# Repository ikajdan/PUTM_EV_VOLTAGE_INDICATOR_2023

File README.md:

# Voltage Indicator

This repository contains the hardware design files for a voltage indicator used in the accumulator of a Formula Student electric vehicle. The voltage indicator is a safety feature that provides a visual indication when the voltage exceeds a safe threshold. The voltage indicator is designed to meet the requirements of the Formula Student EV rulebook and ensure the safety of the accumulator during operation.

The rules state that the connection status must be clearly visible, and electrically controlled switches are not allowed. A visible indicator, such as a voltmeter or red LED, must illuminate when voltage exceeds 60 V DC or half the maximum TS voltage. This indicator must be clearly marked as a "Voltage Indicator", visible during disconnection, and function independently of software control, always powered by the TS, even when the accumulator is removed.

<br>
<div align="center">
  </img>
  <br><br>
  <em>PCB layout of the voltage indicator.</em>
</div>
<br>

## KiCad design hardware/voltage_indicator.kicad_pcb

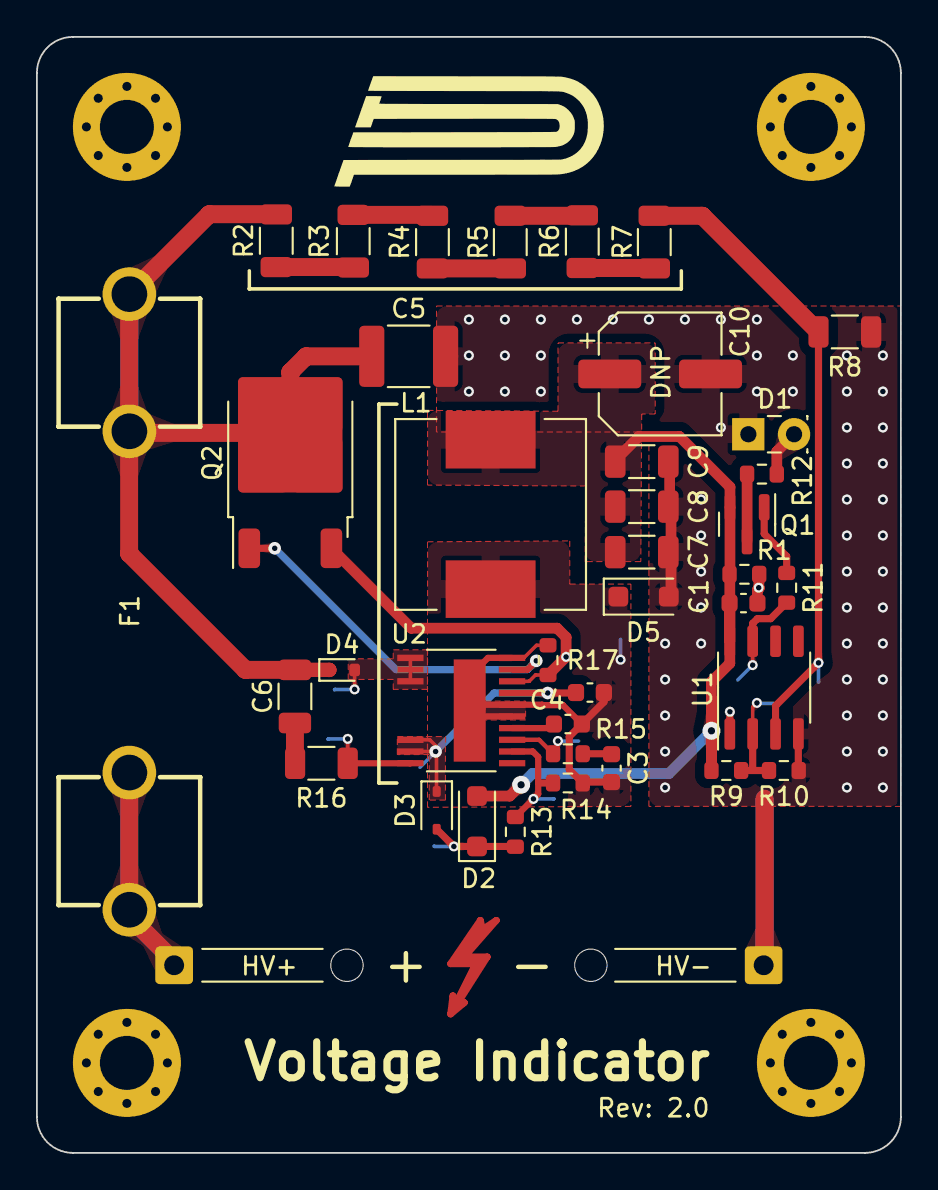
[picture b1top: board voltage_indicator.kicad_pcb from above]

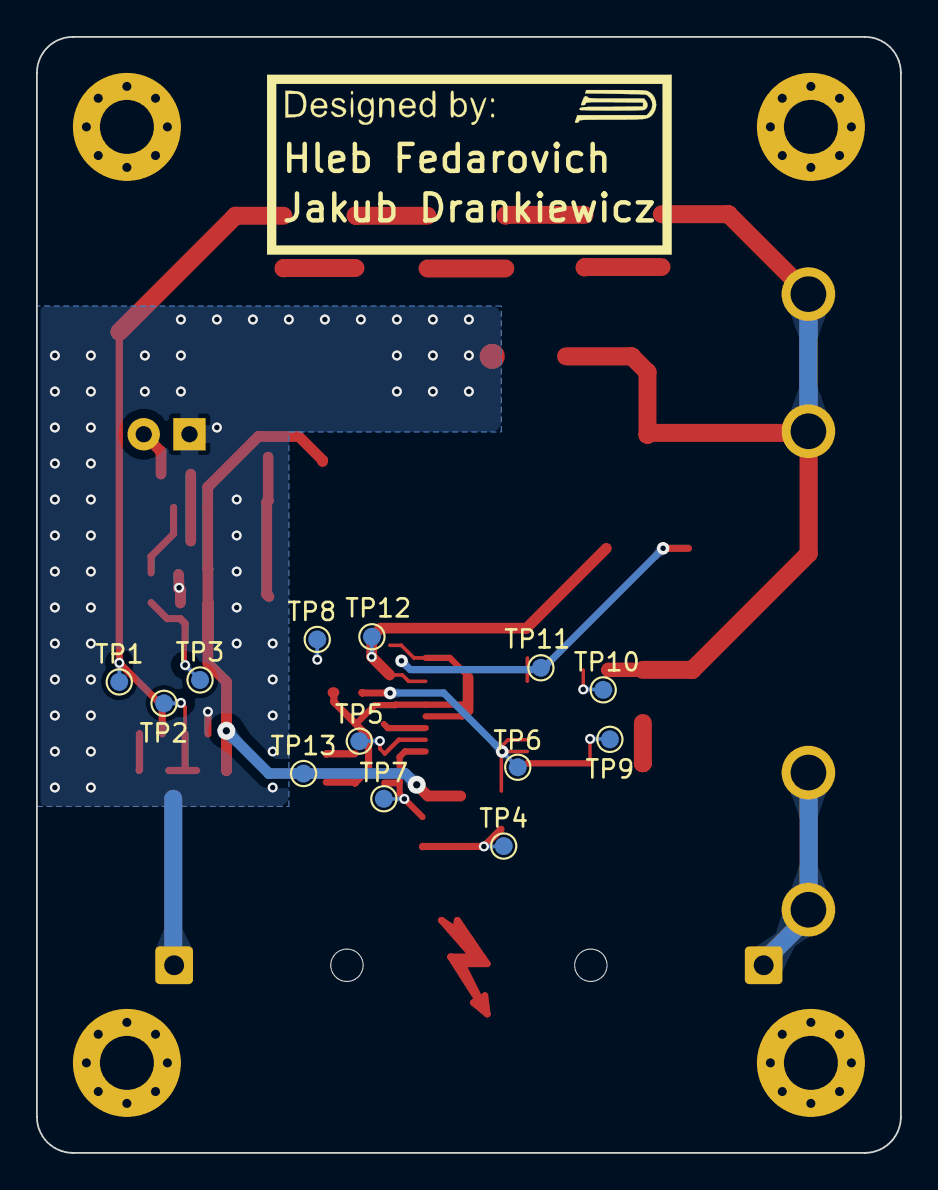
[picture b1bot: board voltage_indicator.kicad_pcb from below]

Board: 2 copper layers, 48.0 x 62.0 mm, 53 parts (13 on the bottom side), 27 nets.

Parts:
C1, C3, C4: 100n; C_0603_1608Metric
C2: 10u; C_0603_1608Metric
C5: 100n; C_1812_4532Metric
C6: 10p; C_1206_3216Metric
C7, C8, C9: 47u; C_1206_3216Metric
C10: 330u; CP_Elec_6.3x5.4
D1: Red; LED_Rectangular_W3.9mm_H1.9mm
D2, D5: US1KFA; D_SOD-123F
D3: CMDSH2-3; D_SOD-323
D4: 10V; D_SOD-523
F1: 600V; FuseClip
J1: HV+; SolderWire_Relief
J2: HV-; SolderWire_Relief
L1: 1m; WurthElektronikInductor_7687714102
Q1: BC807; SOT-23
Q2: TK3P80ERQ; TO-252-2
R1: 1k; R_0603_1608Metric
R2, R3, R4, R5, R6, R7: 100k; R_1206_3216Metric
R8, R16: 10k; R_1206_3216Metric
R9: 3k; R_0603_1608Metric
R10: 240R; R_0603_1608Metric
R11: 1k5; R_0603_1608Metric
R12: 470R; R_0603_1608Metric
R13: 21k5; R_0603_1608Metric
R14: 2k49; R_0603_1608Metric
R15: 22k1; R_0603_1608Metric
R17: 220m; R_0603_1608Metric
TP1: LM_N; TestPoint_Pad_D1.0mm
TP2: LM_P; TestPoint_Pad_D1.0mm
TP3: LM_OUT; TestPoint_Pad_D1.0mm
TP4: LT_D3; TestPoint_Pad_D1.0mm
TP5: LT_VC; TestPoint_Pad_D1.0mm
TP6: LT_BIAS; TestPoint_Pad_D1.0mm
TP7: LT_FB; TestPoint_Pad_D1.0mm
TP8: LT_GND; TestPoint_Pad_D1.0mm
TP9: LT_DCM; TestPoint_Pad_D1.0mm
TP10: LT_VIN; TestPoint_Pad_D1.0mm
TP11: LT_GATE; TestPoint_Pad_D1.0mm
TP12: LT_SENSE; TestPoint_Pad_D1.0mm
TP13: LT_VOUT; TestPoint_Pad_D1.0mm
U1: LM211DT; SO-8_3.9x4.9mm_P1.27mm
U2: LT8316EFE

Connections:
+12V: C1.1, C7.2, C8.2, C9.2, C10.1, D2.2 (A), L1.2, Q1.2 (E), R1.1, R9.2, TP13.1, U1.8 (V+)
GND: C1.2, C5.2, C7.1, C8.1, C9.1, C10.2, D1.1 (K), D5.2 (A), J2.1, R1.2, R8.1, R10.1, U1.1 (GND), U1.4 (V-)
unnamed: C3.1, R15.1
unnamed: C6.1, R16.1
unnamed: D1.2 (A), R12.2
unnamed: D2.1 (K), D3.2 (A), R13.2, TP4.1
unnamed: C2.1, D3.1 (K), TP6.1, U2.8 (INTVCC), U2.9 (BIAS), U2.17 (EN/UVLO)
unnamed: D4.2 (A), TP10.1, U2.1 (VIN), U2.2 (VIN), U2.3 (VIN)
unnamed: C2.2, C3.2, C4.2, D5.1 (K), L1.1, R14.1, R17.1, TP8.1, U2.15 (GND), U2.16 (SMODE), U2.20 (GND), U2.EPAD
unnamed: F1.2, J1.1
unnamed: Q1.1 (B), R11.2
unnamed: Q1.3 (C), R12.1
unnamed: Q2.1 (G), TP11.1, U2.19 (GATE)
unnamed: Q2.3 (S), R17.2, TP12.1, U2.18 (SENSE)
unnamed: R2.1, R3.2
unnamed: R3.1, R4.2
unnamed: R4.1, R5.2
unnamed: R5.1, R6.2
unnamed: R6.1, R7.2
unnamed: R11.1, TP3.1, U1.7
unnamed: R9.1, R10.2, TP2.1, U1.2 (+)
unnamed: R7.1, R8.2, TP1.1, U1.3 (-)
unnamed: R16.2, TP9.1, U2.10 (DCM)
unnamed: R13.1, R14.2, TP7.1, U2.12 (FB)
unnamed: C4.1, U2.14 (IREG/SS)
unnamed: R15.2, TP5.1, U2.13 (VC)
VCC: C5.1, C6.2, D4.1 (K), F1.1, Q2.2 (D), R2.2

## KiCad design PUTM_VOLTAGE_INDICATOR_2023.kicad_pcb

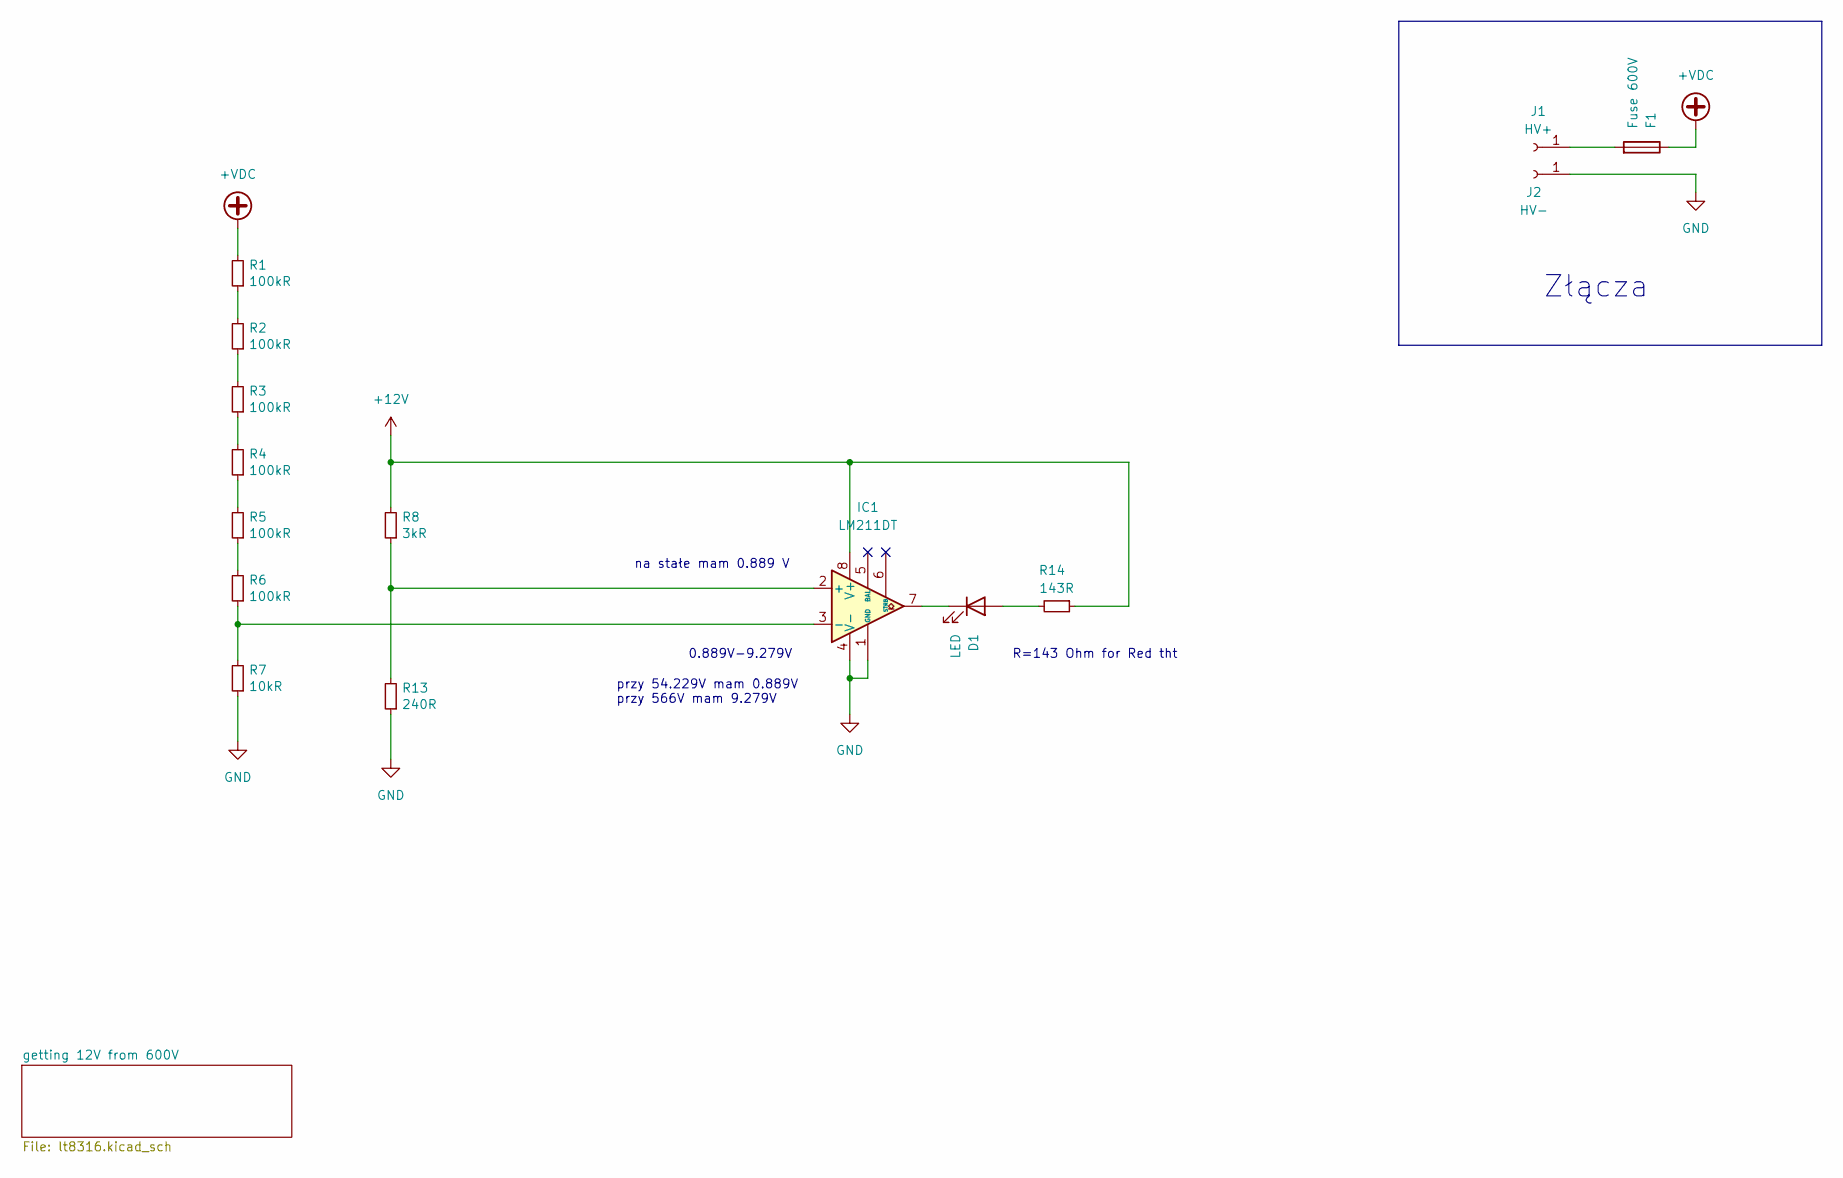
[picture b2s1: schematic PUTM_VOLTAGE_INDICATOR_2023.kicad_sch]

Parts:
D1: LED; LED_D2.0mm_W4.8mm_H2.5mm_FlatTop
F1: Fuse 600V; 01020071Z-FUSE-CLIP
IC1: LM211DT; SO-8_3.9x4.9mm_P1.27mm; Mouser Part Number 511-LM211DT
J1: HV+; SolderWire-0.5sqmm_1x01_D0.9mm_OD2.1mm_Relief
J2: HV-; SolderWire-0.5sqmm_1x01_D0.9mm_OD2.1mm_Relief
R1, R2, R3, R4, R5, R6: 100kR; R_1206_3216Metric
R7: 10kR; R_1206_3216Metric
R8: 3kR; R_0603_1608Metric
R13: 240R; R_0603_1608Metric
R14: 143R; R_0603_1608Metric

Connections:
+12V: IC1.8 (V+), R8.2, R14.1; also elsewhere on the board
+VDC: F1.1, R1.2; also elsewhere on the board
GND: IC1.1 (GND), IC1.4 (V-), J2.1, R7.1, R13.1; also elsewhere on the board
unnamed: D1.1 (K), IC1.7
unnamed: D1.2 (A), R14.2
unnamed: F1.2, J1.1
unnamed: IC1.2 (+), R8.1, R13.2
unnamed: IC1.3 (-), R6.1, R7.2
unnamed: R1.1, R2.2
unnamed: R2.1, R3.2
unnamed: R3.1, R4.2
unnamed: R4.1, R5.2
unnamed: R5.1, R6.2

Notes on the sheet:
Złącza
R=143 Ohm for Red tht
przy 54.229V mam 0.889V przy 566V mam 9.279V
na stałe mam 0.889 V
0.889V-9.279V

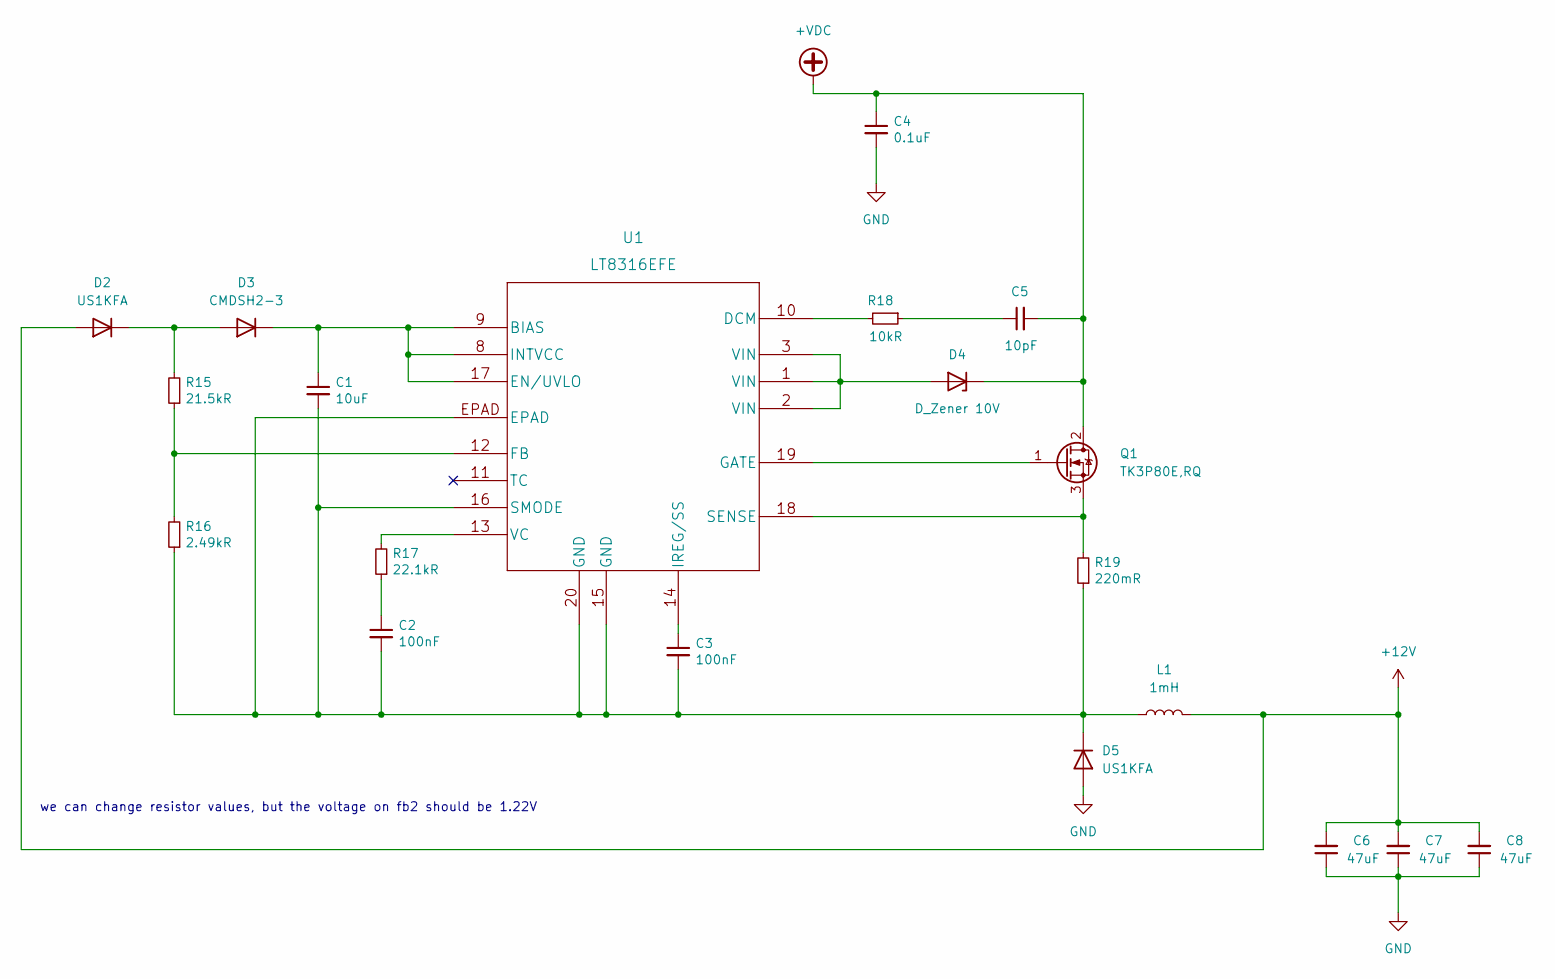
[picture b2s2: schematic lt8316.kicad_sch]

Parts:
C1: 10uF; C_0603_1608Metric
C2, C3: 100nF; C_0603_1608Metric
C4: 0.1uF; C_1812_4532Metric
C5: 10pF; C_1206_3216Metric
C6, C7, C8: 47uF; C_1206_3216Metric
D2, D5: US1KFA; D_SOD-123F
D3: CMDSH2-3; D_SOD-323
D4: D_Zener 10V; D_SOD-523
L1: 1mH; L_Wuerth_WE-PD2-Typ-MS
Q1: TK3P80E,RQ; TO-252-2; Manufacturer_Part_Number TK3P80E,RQ
R15: 21.5kR; R_0603_1608Metric
R16: 2.49kR; R_0603_1608Metric
R17: 22.1kR; R_0603_1608Metric
R18: 10kR; R_1206_3216Metric
R19: 220mR; R_0603_1608Metric
U1: LT8316EFE

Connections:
+12V: C6.2, C7.2, C8.2, D2.2 (A), L1.2; also elsewhere on the board
+VDC: C4.1, C5.2, D4.1 (K), Q1.2 (D); also elsewhere on the board
GND: C4.2, C6.1, C7.1, C8.1, D5.2 (A); also elsewhere on the board
unnamed: C1.1, D3.2 (K), U1.8 (INTVCC), U1.9 (BIAS), U1.17 (EN/UVLO)
unnamed: C1.2, C2.2, C3.2, D5.1 (K), L1.1, R16.1, R19.1, U1.15 (GND), U1.16 (SMODE), U1.20 (GND), U1.EPAD
unnamed: C2.1, R17.1
unnamed: C3.1, U1.14 (IREG/SS)
unnamed: C5.1, R18.1
unnamed: D2.1 (K), D3.1 (A), R15.2
unnamed: D4.2 (A), U1.1 (VIN), U1.2 (VIN), U1.3 (VIN)
unnamed: Q1.1 (G), U1.19 (GATE)
unnamed: Q1.3 (S), R19.2, U1.18 (SENSE)
unnamed: R15.1, R16.2, U1.12 (FB)
unnamed: R17.2, U1.13 (VC)
unnamed: R18.2, U1.10 (DCM)

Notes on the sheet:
we can change resistor values, but the voltage on fb2 should be 1.22V

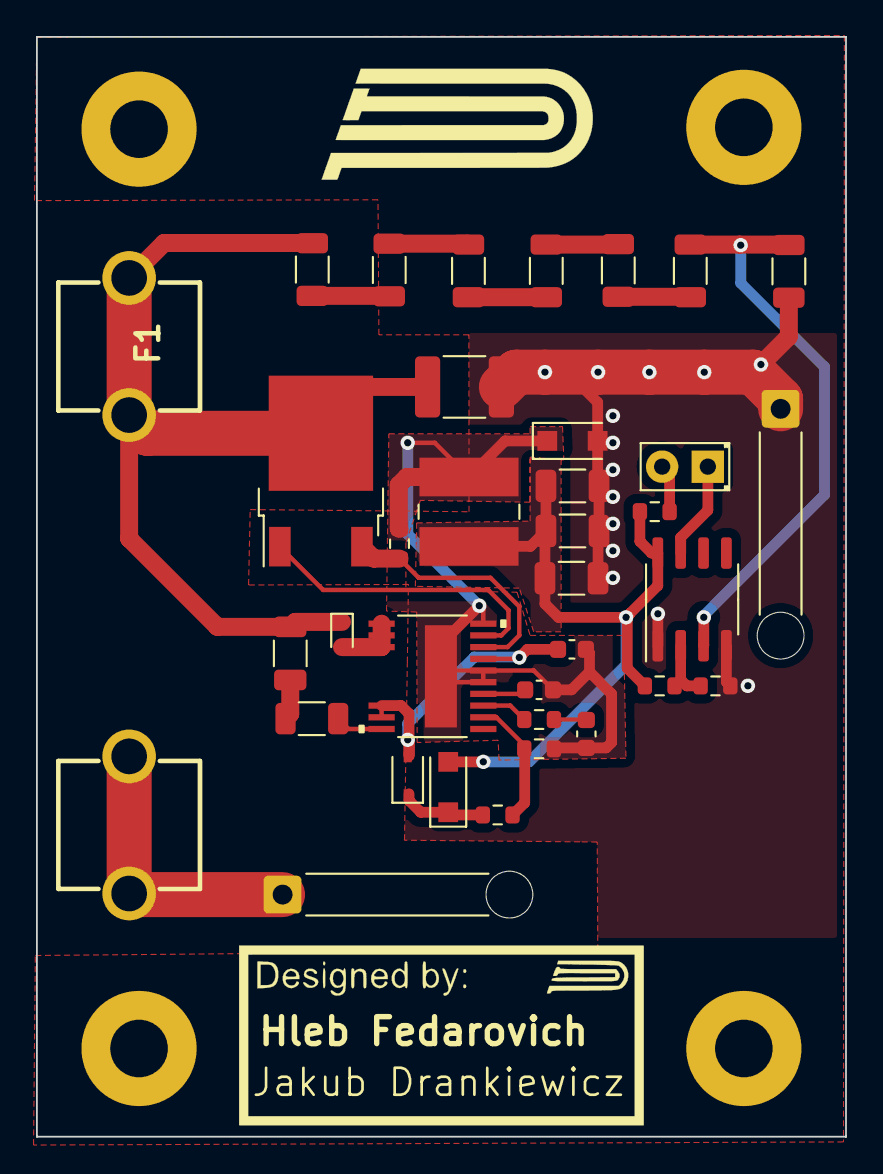
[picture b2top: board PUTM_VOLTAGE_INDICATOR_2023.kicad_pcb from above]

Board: 2 copper layers, 44.9 x 61.1 mm, 35 parts (0 on the bottom side), 25 nets.

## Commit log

2022-11-29 change scheme of LT8316EFE and change mosfet symbol
2022-12-06 add all the needed components
2022-12-06 gitignore change + capacitors improve
2022-12-06 dodaję fus, wybieram led, zmieniam komparator, dodaję datasheety
2022-12-09 add resistors / add footprints and datasheets/ change symbols
2022-12-10 add pcb
2022-12-11 resistors change; elements placed; new footprints
2022-12-11 pcb edit
2022-12-11 pcb update
    Changed converter layout, fuse footprint
2022-12-11 Update PUTM_VOLTAGE_INDICATOR_2023.kicad_pcb
    pcb update
2022-12-11 pcb update
2022-12-11 cleanup
    cleaned up some traces, fixed DRC errors
2022-12-13 symbol changed / resistor values changed
2022-12-14 fuse position changed/ small pcb updates
2022-12-15 pcb update / resistor values
2023-03-26 Cleanup the project
2023-05-06 Improve the layout
2023-05-06 Remove teardrops from SMD pads
2023-05-07 Use a transistor to drive the LED
2023-05-07 Align the signature box
2023-07-06 Update component values
2025-07-27 Update the README

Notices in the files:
parts and their libraries:
Copyright 2021 Accelerated Designs. All rights reserved.
